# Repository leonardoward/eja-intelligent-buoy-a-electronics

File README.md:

# EJA Intelligent Buoy A - Electronic Design

EJA Intelligent Buoy A - Electronic Design - [2020 Hackaday Dream Team Challenge for Conservation X Labs](https://hackaday.io/project/173457-2020-hdp-dream-team-conservation-x-labs).

Buoy A is a 141.73 mm x 54.86 mm PCB that integrates 5 main modules (ESP32, LoRa, GPS, Motor Driver and GSM/GPRS).

This repository contains the KiCad design for the PCB of the Intelligent Buoy A. It also contains the 3D models used to visualize the design in the KiCad 3D viewer.

## Context

**EJA** is a pop‑up recovery buoy for lost fishing gear. A buoy sits on the seabed
attached to a trap or net; a scheduled timer (or a command over LoRa from the
[Onboard Gateway](https://github.com/leonardoward/eja-onboard-gateway-electronics))
releases it, it floats up, and its GPS position is reported so the gear can be
recovered. **Buoy A** is the fuller variant &mdash; it adds a **TB6612FNG** motor driver
for the release actuator and an optional **SIM7600 GSM/GPRS** shield for a cellular
uplink where there is coverage. It runs the
[Buoy firmware](https://github.com/leonardoward/eja-intelligent-buoy-b-firmware).
The single‑board successor that folds this whole system onto one PCB is
[EJA M](https://github.com/leonardoward/eja-m-pcb-design).

## Main Components ##

Sources:

- [ESP32-DEVKITC-32D](https://www.digikey.com/product-detail/es/espressif-systems/ESP32-DEVKITC-32D/1965-1000-ND/9356990)
- [RFM95W LoRa Radio](https://www.digikey.com/product-detail/es/adafruit-industries-llc/3072/1528-1667-ND/6005357)
- [TB6612FNG MOTOR DRIVER BOARD](https://www.digikey.com/product-detail/es/sparkfun-electronics/ROB-14450/1568-1755-ND/7915576)
- [Adafruit Ultimate GPS](https://www.digikey.com/product-detail/es/adafruit-industries-llc/746/1528-1153-ND/5353613)
- [SIM7600CE-T 4G(LTE) Arduino Shield](https://www.mouser.com/ProductDetail/DFRobot/TEL0124?qs=17u8i%2FzlE88MEbXRJuYFsA==)

## Schematic ##

[For a detailed explanation of the schematic visit the following log.](https://hackaday.io/project/173457/log/181830-buoy-a-v10-schematic-and-pcb-design)

## PCB Layout ##

## Assembly ##

Components List:

1. [ESP32-DEVKITC-32D](https://www.digikey.com/product-detail/es/espressif-systems/ESP32-DEVKITC-32D/1965-1000-ND/9356990)
2. [TB6612FNG MOTOR DRIVER BOARD](https://www.digikey.com/product-detail/es/sparkfun-electronics/ROB-14450/1568-1755-ND/7915576)
3. [CONN HDR 5POS 0.1 GOLD PCB](https://www.digikey.com/product-detail/es/sullins-connector-solutions/PPTC051LFBN-RC/S6103-ND/807239)
4. [CONN HEADER VERT 3POS 2.54MM](https://www.digikey.com/product-detail/es/jst-sales-america-inc/S2B-XH-A-1-LF-SN/455-4226-ND/9961922)
5. [CONN HDR 6POS 0.1 TIN PCB](https://www.digikey.com/product-detail/es/sullins-connector-solutions/PPTC061LFBN-RC/S7004-ND/810145)
6. [CONN HDR 8POS 0.1 TIN PCB](https://www.digikey.com/product-detail/es/sullins-connector-solutions/PPTC081LFBN-RC/S7006-ND/810147)
7. [CONN HDR 8POS 0.1 TIN PCB](https://www.digikey.com/product-detail/es/sullins-connector-solutions/PPTC081LFBN-RC/S7006-ND/810147)
8. [CONN HDR 8POS 0.1 TIN PCB](https://www.digikey.com/product-detail/es/sullins-connector-solutions/PPTC081LFBN-RC/S7006-ND/810147)
9. [CONN HDR 19POS 0.1 TIN PCB](https://www.digikey.com/product-detail/es/sullins-connector-solutions/PPTC191LFBN-RC/S7017-ND/810157)
10. [CONN HDR 19POS 0.1 TIN PCB](https://www.digikey.com/product-detail/es/sullins-connector-solutions/PPTC191LFBN-RC/S7017-ND/810157)
11. PCB Buoy A V1.0
12. [CONN HEADER R/A 3POS 2.5MM](https://www.digikey.com/product-detail/es/jst-sales-america-inc/S3B-XH-A-1-LF-SN/455-2954-ND/1556255)
13. [TERM BLK 3P SIDE ENT 5.08MM PCB](https://www.digikey.com/product-detail/es/on-shore-technology-inc/OSTTC032162/ED2610-ND/614559)
14. [TERM BLK 2P SIDE ENT 5.08MM PCB](https://www.digikey.com/product-detail/es/on-shore-technology-inc/OSTTC022162/ED2609-ND/614558)
15. [CONN HDR 9POS 0.1 GOLD PCB](https://www.digikey.com/product-detail/es/sullins-connector-solutions/PPPC091LFBN-RC/S7042-ND/810181)
16. [CONN HDR 9POS 0.1 GOLD PCB](https://www.digikey.com/product-detail/es/sullins-connector-solutions/PPPC091LFBN-RC/S7042-ND/810181)
17. 2 [CONN HDR 2POS 0.1 GOLD PCB](https://www.digikey.com/product-detail/es/sullins-connector-solutions/PPPC021LFBN-RC/S7035-ND/810174)
18. [CONN HDR 9POS 0.1 GOLD PCB](https://www.digikey.com/product-detail/es/sullins-connector-solutions/PPPC091LFBN-RC/S7042-ND/810181)
19. [CONN HDR 10POS 0.1 TIN PCB](https://www.digikey.com/product-detail/es/sullins-connector-solutions/PPTC101LFBN-RC/S7008-ND/810149)
20. [CONN HEADER VERT 3POS 2.54MM](https://www.digikey.com/product-detail/es/jst-sales-america-inc/S2B-XH-A-1-LF-SN/455-4226-ND/9961922)
21. [Adafruit Ultimate GPS](https://www.digikey.com/product-detail/es/adafruit-industries-llc/746/1528-1153-ND/5353613)
22. [RFM95W LoRa Radio](https://www.digikey.com/product-detail/es/adafruit-industries-llc/3072/1528-1667-ND/6005357)
23. [SIM7600CE-T 4G(LTE) Arduino Shield](https://www.mouser.com/ProductDetail/DFRobot/TEL0124?qs=17u8i%2FzlE88MEbXRJuYFsA==)

[For a detailed Bill of Materials visit the following log.](https://hackaday.io/project/173457/log/183798-buoy-a-v10-bill-of-materials)

[For a detailed explanation about the soldering and assembly procedure visit the following log.](https://hackaday.io/project/173457/log/183738-buoy-a-v10-assembly)

## Wiring Diagrams ##

The following diagrams present the physical connections of the different boards and components of the Buoy A V1.0.

### Battery Management ###

The original design of the board considered the following components:

- Battery (5V < Voltage < 15V)
- PCB Board Buoy A V1.0
- Buck Converter
- Switch
- Extra capacitor

Similar to Buoy B, there is an alternative for the battery management, is possible to provide the required voltages with a boost converter and a 3.7V Battery, like the following example:

- 3.7V 1 Cell Battery
- PCB Board Buoy A V1.0
- Boost Converter
- Micro USB Breakout Board
- Switch
- Extra capacitor
- JST-XH 2 Pos female connector and a JST-XH 2 Pos male connector
- 5V Charger (only used to charge the battery)

This alternative is valid and possible, but is not ideal for longer working time (compared to the first one). It is important to consider the efficiency of the boost converter. The selected boost converter will have a voltage drop at a current higher than 500mA, that should be taken into consideration.

### Motors ###

The board was designed to handle 2 different types of motors, those are:

- Servo Motor

- DC Motor (using the driver TB6612FNG)

[For more information about the wiring diagrams and the project visit the following log.](https://hackaday.io/project/173457/log/182856-buoy-a-v10-wiring-diagrams)

## Future improvements ##

[For more information about the recommended future improvements for the electronic design visit the following log.](https://hackaday.io/project/173457/log/183807-future-improvements-pcb-design)

## Repository Layout

```
Buoy_WithGSM.sch / .kicad_pcb        KiCad 5 project (schematic + board)
Buoy_WithGSM.pro / .net              project + netlist
Symbols/  Footprints/  3D/  step/    project-local libraries and 3D models
Gerber/                              fabrication output
Assembly/                            assembly reference photos
Wiring_Diagrams/                     board-to-component wiring (battery, servo, DC motor)
pdf/  plot/                          exported schematic / layout PDFs
img/                                 renders and photos used in this README
LICENSE                              Apache 2.0
```

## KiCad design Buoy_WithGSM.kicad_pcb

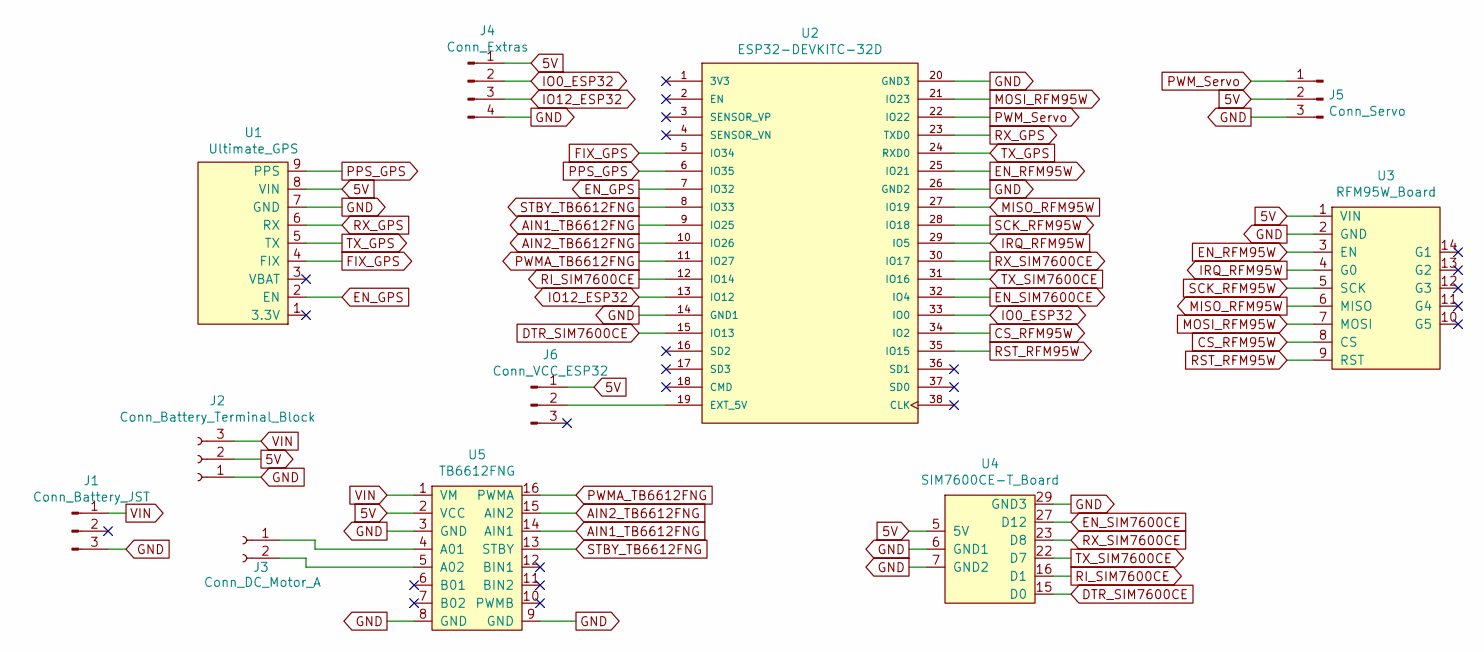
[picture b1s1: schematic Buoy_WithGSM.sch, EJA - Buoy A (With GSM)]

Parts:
J1: Conn_Battery_JST; JST_XH_S3B-XH-A-1_1x03_P2.50mm_Horizontal
J2: Conn_Battery_Terminal_Block; TerminalBlock_bornier-3_P5.08mm
J3: Conn_DC_Motor_A; TerminalBlock_bornier-2_P5.08mm
J4: Conn_Extras; PinSocket_1x04_P2.54mm_Vertical
J5: Conn_Servo; PinHeader_1x03_P2.54mm_Vertical
J6: Conn_VCC_ESP32; PinHeader_1x03_P2.54mm_Vertical
U1: Ultimate_GPS
U2: ESP32-DEVKITC-32D; MODULE_ESP32-DEVKITC-32D
U3: RFM95W_Board; RFM95W-Board
U4: SIM7600CE-T_Board
U5: TB6612FNG

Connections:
5V: J2.2, J4.1, J5.2, J6.1, U1.8 (VIN), U3.1 (VIN), U4.5 (5V), U5.2 (VCC)
AIN1_TB6612FNG: U2.9 (IO25), U5.14 (AIN1)
AIN2_TB6612FNG: U2.10 (IO26), U5.15 (AIN2)
CS_RFM95W: U2.34 (IO2), U3.8 (CS)
DTR_SIM7600CE: U2.15 (IO13), U4.15 (D0)
EN_GPS: U1.2 (EN), U2.7 (IO32)
EN_RFM95W: U2.25 (IO21), U3.3 (EN)
EN_SIM7600CE: U2.32 (IO4), U4.27 (D12)
FIX_GPS: U1.4 (FIX), U2.5 (IO34)
GND: J1.3, J2.1, J4.4, J5.3, U1.7 (GND), U2.14 (GND1), U2.20 (GND3), U2.26 (GND2), U3.2 (GND), U4.6 (GND1), U4.7 (GND2), U4.29 (GND3), U5.3 (GND), U5.8 (GND), U5.9 (GND)
IO0_ESP32: J4.2, U2.33 (IO0)
IO12_ESP32: J4.3, U2.13 (IO12)
IRQ_RFM95W: U2.29 (IO5), U3.4 (G0)
MISO_RFM95W: U2.27 (IO19), U3.6 (MISO)
MOSI_RFM95W: U2.21 (IO23), U3.7 (MOSI)
unnamed: J3.1, U5.4 (A01)
unnamed: J3.2, U5.5 (A02)
unnamed: J6.2, U2.19 (EXT_5V)
PPS_GPS: U1.9 (PPS), U2.6 (IO35)
PWMA_TB6612FNG: U2.11 (IO27), U5.16 (PWMA)
PWM_Servo: J5.1, U2.22 (IO22)
RI_SIM7600CE: U2.12 (IO14), U4.16 (D1)
RST_RFM95W: U2.35 (IO15), U3.9 (RST)
RX_GPS: U1.6 (RX), U2.23 (TXD0)
RX_SIM7600CE: U2.30 (IO17), U4.23 (D8)
SCK_RFM95W: U2.28 (IO18), U3.5 (SCK)
STBY_TB6612FNG: U2.8 (IO33), U5.13 (STBY)
TX_GPS: U1.5 (TX), U2.24 (RXD0)
TX_SIM7600CE: U2.31 (IO16), U4.22 (D7)
VIN: J1.1, J2.3, U5.1 (VM)

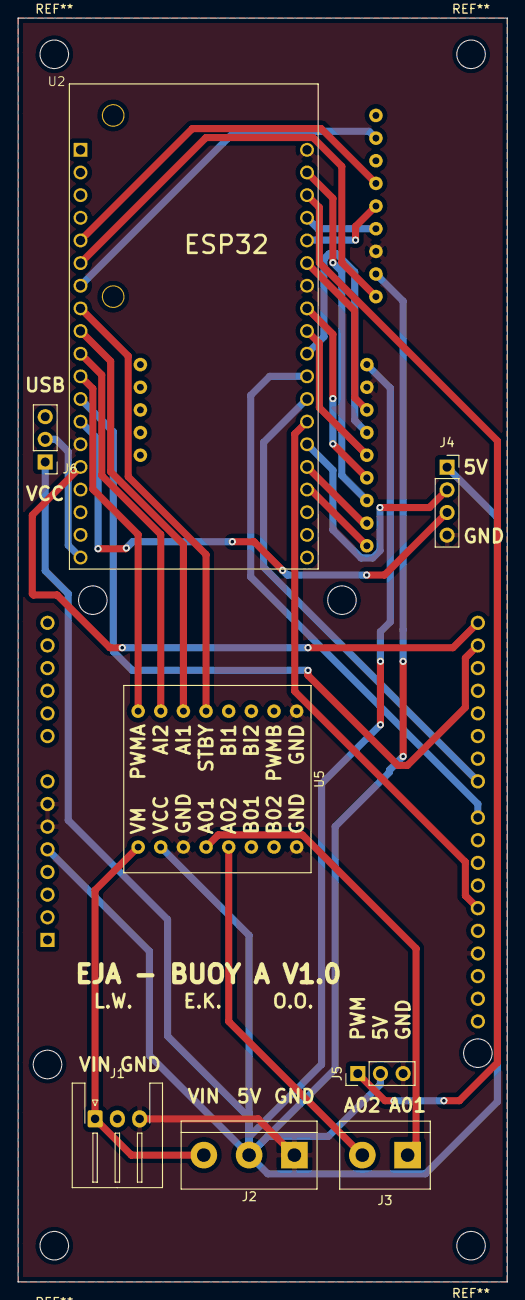
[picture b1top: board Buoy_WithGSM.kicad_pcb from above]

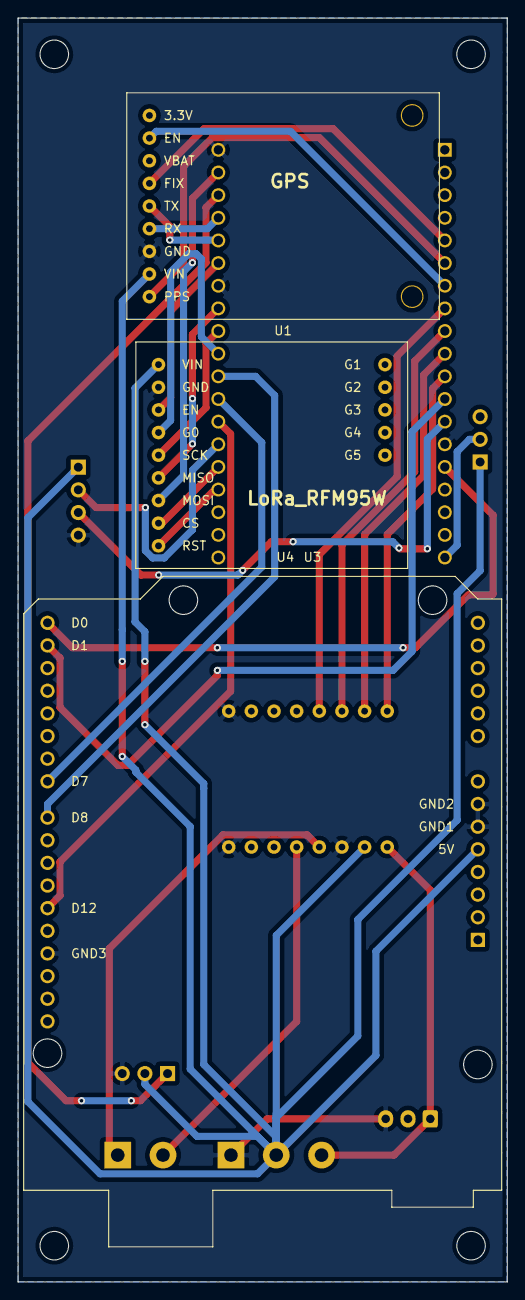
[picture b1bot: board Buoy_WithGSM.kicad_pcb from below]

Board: 2 copper layers, 54.9 x 141.7 mm, 11 parts (2 on the bottom side), 30 nets.

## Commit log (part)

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2020-09-28 Added KiCad design
2020-09-28 Added wiring diagrams and assembly guide
2020-09-28 Fixed image routes
2020-09-28 Added PCB image
2020-09-28 Changed pcb image
2020-09-28 Added components image
2020-09-28 Added components list
2020-09-28 Added links to hackaday page
2020-09-28 Added future improvements
